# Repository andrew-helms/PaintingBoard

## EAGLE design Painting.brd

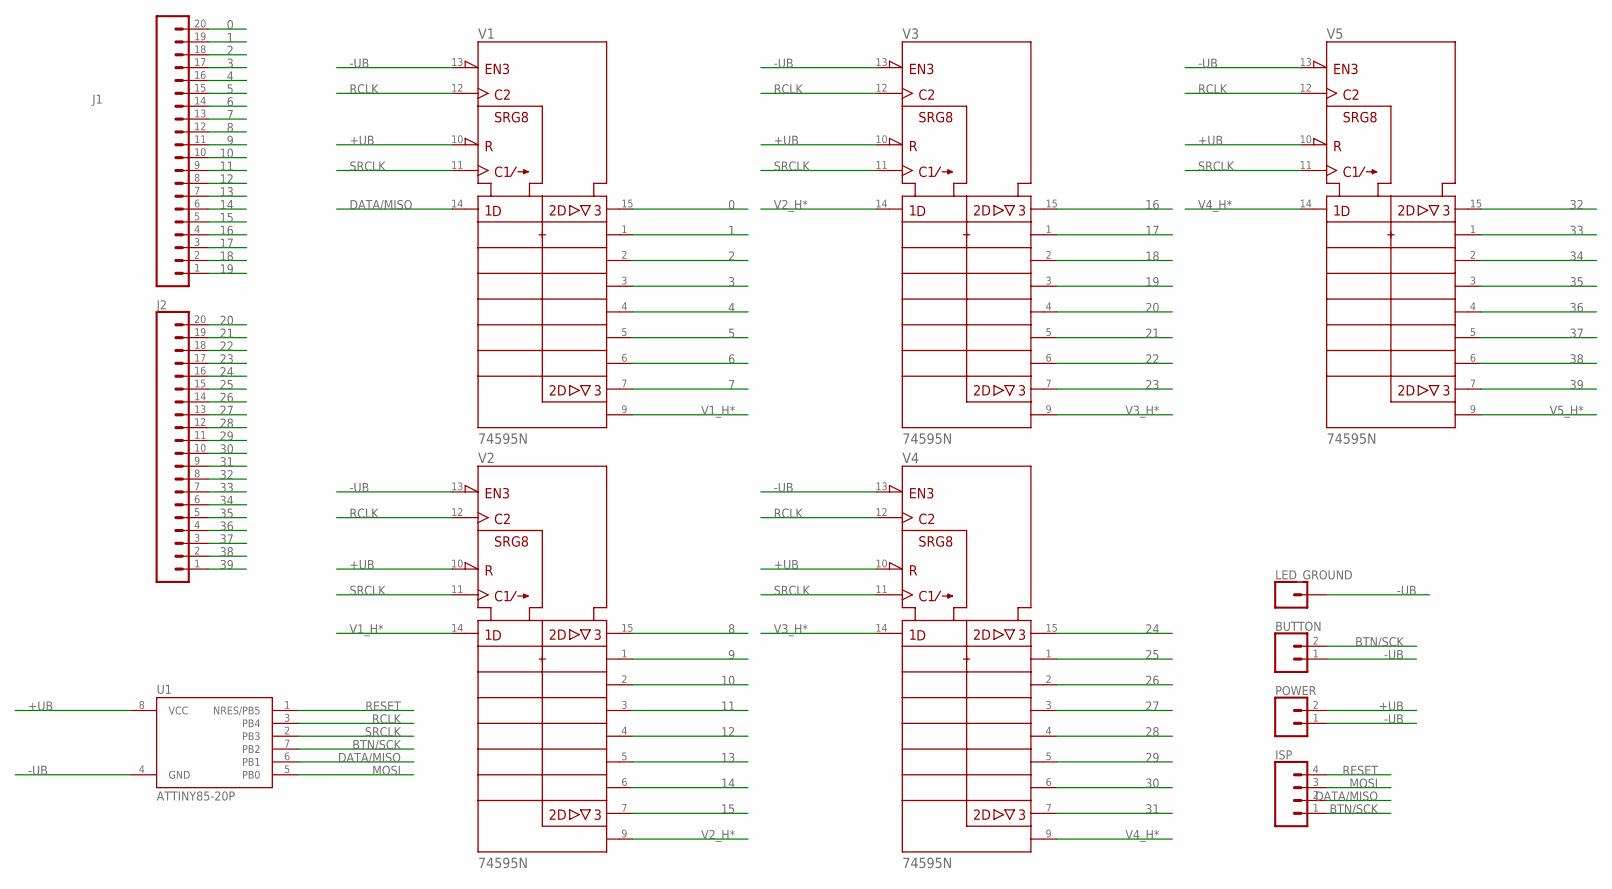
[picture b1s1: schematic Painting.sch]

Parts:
BUTTON: CONN_02PTH3; 1X02_LONGPADS
ISP: CONN_04LONGPADS; 1X04_LONGPADS
J1, J2: CONN_20; 1X20
LED_GROUND: CONN_01PTH_LONGPAD; 1X01_LONGPAD
POWER: CONN_02PTH3; 1X02_LONGPADS
U1: ATTINY85-20P; PDIP08_300MIL
V1, V2, V3, V4, V5: 74595N; DIL16

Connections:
0: J1.20, V1.15 (QA)
1: J1.19, V1.1 (QB)
2: J1.18, V1.2 (QC)
3: J1.17, V1.3 (QD)
4: J1.16, V1.4 (QE)
5: J1.15, V1.5 (QF)
6: J1.14, V1.6 (QG)
7: J1.13, V1.7 (QH)
8: J1.12, V2.15 (QA)
9: J1.11, V2.1 (QB)
10: J1.10, V2.2 (QC)
11: J1.9, V2.3 (QD)
12: J1.8, V2.4 (QE)
13: J1.7, V2.5 (QF)
14: J1.6, V2.6 (QG)
15: J1.5, V2.7 (QH)
16: J1.4, V3.15 (QA)
17: J1.3, V3.1 (QB)
18: J1.2, V3.2 (QC)
19: J1.1, V3.3 (QD)
20: J2.20, V3.4 (QE)
21: J2.19, V3.5 (QF)
22: J2.18, V3.6 (QG)
23: J2.17, V3.7 (QH)
24: J2.16, V4.15 (QA)
25: J2.15, V4.1 (QB)
26: J2.14, V4.2 (QC)
27: J2.13, V4.3 (QD)
28: J2.12, V4.4 (QE)
29: J2.11, V4.5 (QF)
30: J2.10, V4.6 (QG)
31: J2.9, V4.7 (QH)
32: J2.8, V5.15 (QA)
33: J2.7, V5.1 (QB)
34: J2.6, V5.2 (QC)
35: J2.5, V5.3 (QD)
36: J2.4, V5.4 (QE)
37: J2.3, V5.5 (QF)
38: J2.2, V5.6 (QG)
39: J2.1, V5.7 (QH)
+UB: POWER.2, U1.8 (VCC), V1.10 (!SRCLR), V1.16 (+UB), V2.10 (!SRCLR), V2.16 (+UB), V3.10 (!SRCLR), V3.16 (+UB), V4.10 (!SRCLR), V4.16 (+UB), V5.10 (!SRCLR), V5.16 (+UB)
-UB: BUTTON.1, LED_GROUND.1, POWER.1, U1.4 (GND), V1.8 (-UB), V1.13 (!G), V2.8 (-UB), V2.13 (!G), V3.8 (-UB), V3.13 (!G), V4.8 (-UB), V4.13 (!G), V5.8 (-UB), V5.13 (!G)
BTN/SCK: BUTTON.2, ISP.1, U1.7 (PB2)
DATA/MISO: ISP.2, U1.6 (PB1), V1.14 (SER)
MOSI: ISP.3, U1.5 (PB0)
RCLK: U1.3 (PB4), V1.12 (RCK), V2.12 (RCK), V3.12 (RCK), V4.12 (RCK), V5.12 (RCK)
RESET: ISP.4, U1.1 (NRES/PB5)
SRCLK: U1.2 (PB3), V1.11 (SRCK), V2.11 (SRCK), V3.11 (SRCK), V4.11 (SRCK), V5.11 (SRCK)
V1_H*: V1.9 (QH*), V2.14 (SER)
V2_H*: V2.9 (QH*), V3.14 (SER)
V3_H*: V3.9 (QH*), V4.14 (SER)
V4_H*: V4.9 (QH*), V5.14 (SER)
V5_H*: V5.9 (QH*)

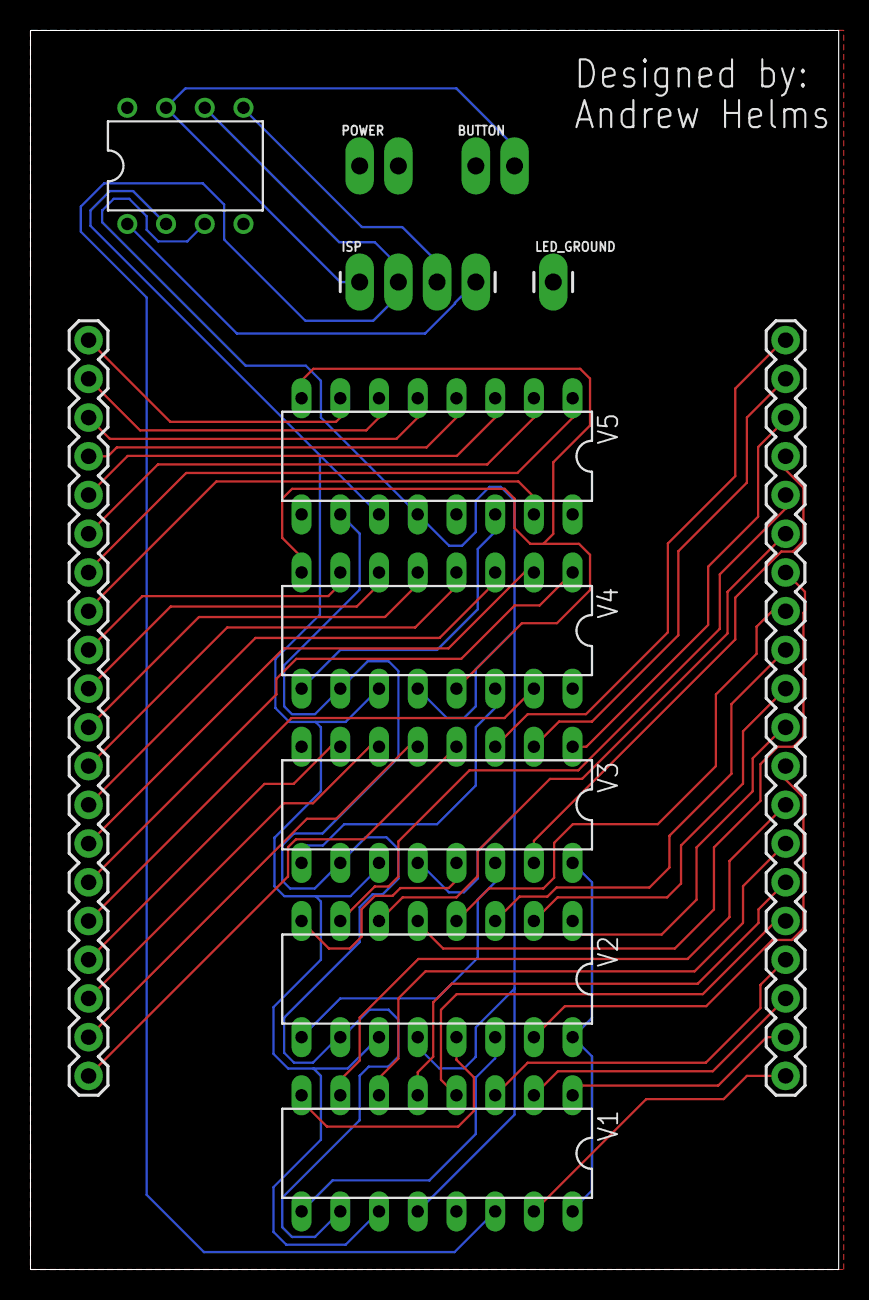
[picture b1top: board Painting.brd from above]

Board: 2 copper layers, 53.0 x 81.3 mm, 12 parts (0 on the bottom side), 52 nets.

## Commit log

2020-09-08 First Draft
2020-09-08 Removing 90 degrees in traces
2020-09-09 Increased trace spacing and deleted backup files
    Read the commit message title
2020-09-09 Connected another trace and wrote some more words
2020-09-10 Added components for resistors

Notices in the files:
parts and their libraries:
SparkFun-Connectors: Licensing: Creative Commons ShareAlike 4.0 International - https://creativecommons.org/licenses/by-sa/4.0
